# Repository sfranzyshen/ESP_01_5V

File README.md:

Convert ESP-01 to use 5 volts
# ESP_01_5V

#Fourm Post:
http://www.esp8266.com/viewtopic.php?f=13&t=2187&p=12962

#oshpark.com - order pcb
https://oshpark.com/shared_projects/epBbPet4

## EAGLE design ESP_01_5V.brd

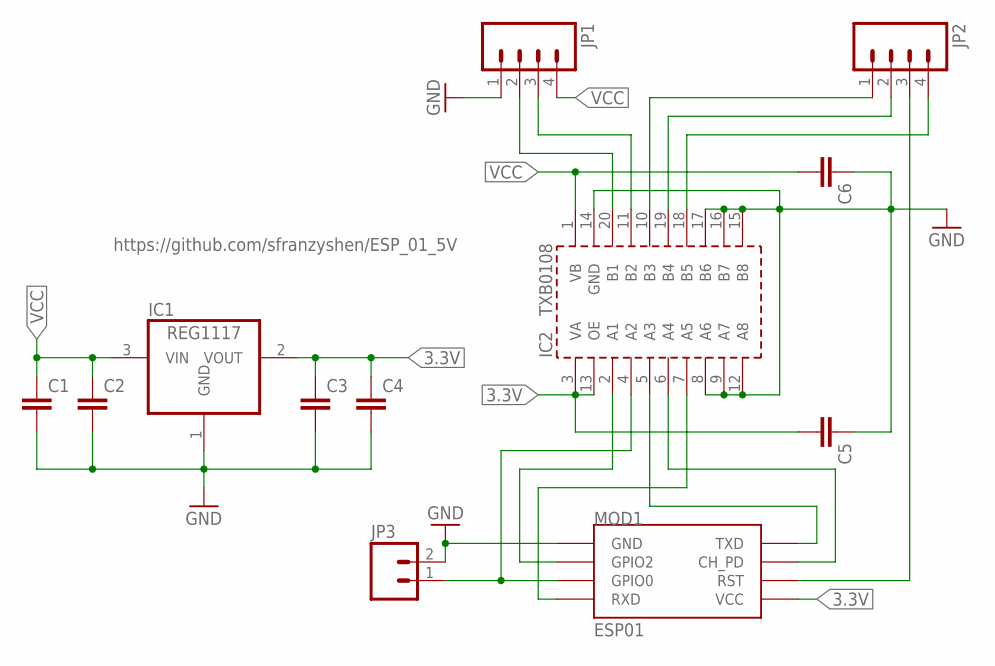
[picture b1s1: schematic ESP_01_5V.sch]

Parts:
C1, C2, C3, C4, C5, C6: CAP0603-CAP; 0603-CAP
IC1: REG1117; SOT223
IC2: IC_TXB0108-TSSOP-20; TSSOP-20
JP1, JP2: .1" 4 Pin Male; 1X04
JP3: M02PTH; 1X02
MOD1: ESP01

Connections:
3.3V: C3.1, C4.1, C5.2, IC1.2 (VOUT), IC2.3 (VA), IC2.13 (OE), MOD1.VCC
GND: C1.2, C2.2, C3.2, C4.2, C5.1, C6.1, IC1.1 (GND), IC2.8 (A6), IC2.9 (A7), IC2.12 (A8), IC2.14 (GND), IC2.15 (B8), IC2.16 (B7), IC2.17 (B6), JP1.1, JP3.2, MOD1.GND
unnamed: IC2.20 (B1), JP1.2
unnamed: IC2.11 (B2), JP1.3
unnamed: IC2.10 (B3), JP2.1
unnamed: IC2.19 (B4), JP2.2
unnamed: IC2.18 (B5), JP2.4
unnamed: JP2.3, MOD1.RST
unnamed: IC2.7 (A5), MOD1.RX (RXD)
unnamed: IC2.2 (A1), MOD1.GPIO2
unnamed: IC2.4 (A2), JP3.1, MOD1.GPIO0
unnamed: IC2.5 (A3), MOD1.TX (TXD)
unnamed: IC2.6 (A4), MOD1.CH_PD
VCC: C1.1, C2.1, C6.2, IC1.3 (VIN), IC2.1 (VB), JP1.4

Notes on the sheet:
TXB0108
https://github.com/sfranzyshen/ESP_01_5V

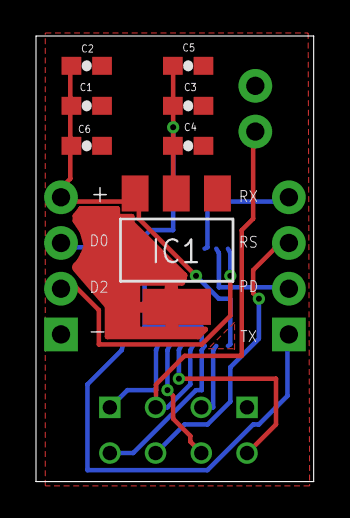
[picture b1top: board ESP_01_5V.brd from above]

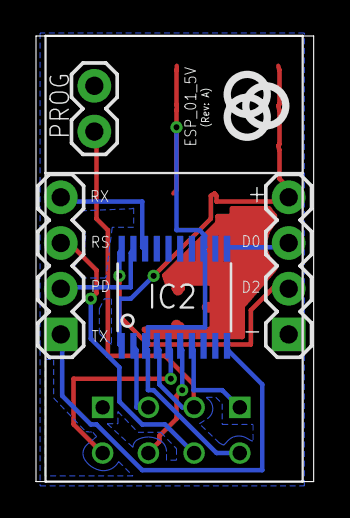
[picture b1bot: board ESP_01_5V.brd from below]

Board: 2 copper layers, 15.4 x 24.8 mm, 12 parts (5 on the bottom side), 14 nets.

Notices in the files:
parts and their libraries:
SparkFun-Capacitors: Licensing: Creative Commons ShareAlike 4.0 International - https://creativecommons.org/licenses/by-sa/4.0
